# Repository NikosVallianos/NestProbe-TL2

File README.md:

# TL2 Low Cost/Power/Size High Precision Temperature Logger

This is the complete repository for the TL2 low cost/power/size temperature logger. It includes schematic and PCB layout files in EagleCAD and firmware for the ATtiny816 MCU. The Eagle files are final but the firmware is currently under prototyping-phase development and not yet published.

# List of primary components and documentation
This is a listing of the primary components used on the TL2 and links to their manufacturer's product page, where more documentation can be found.

- MCU: [Atmel/Microchip ATtiny816](https://www.microchip.com/wwwproducts/en/ATTINY816)
- Temperature sensor: [Silicon Labs Si7051](https://www.silabs.com/products/sensors/temperature/si705x/device.si7051)
- Data storage EEPROM: [Adesto AT25DN512C](https://www.adestotech.com/wp-content/uploads/DS-AT25DN512C_037.pdf) (datasheet, no product page)
- Real time clock 32.768kHz crystal: [ECS ECX-31B](https://ecsxtal.com/ecx-31b)
- Indicator amber color LED: [Kingbright APHHS1005SYCK](http://www.kingbrightusa.com/images/catalog/SPEC/APHHS1005SYCK.pdf)

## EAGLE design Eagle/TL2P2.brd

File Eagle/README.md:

Eagle cad files of the TL2 temperature logger

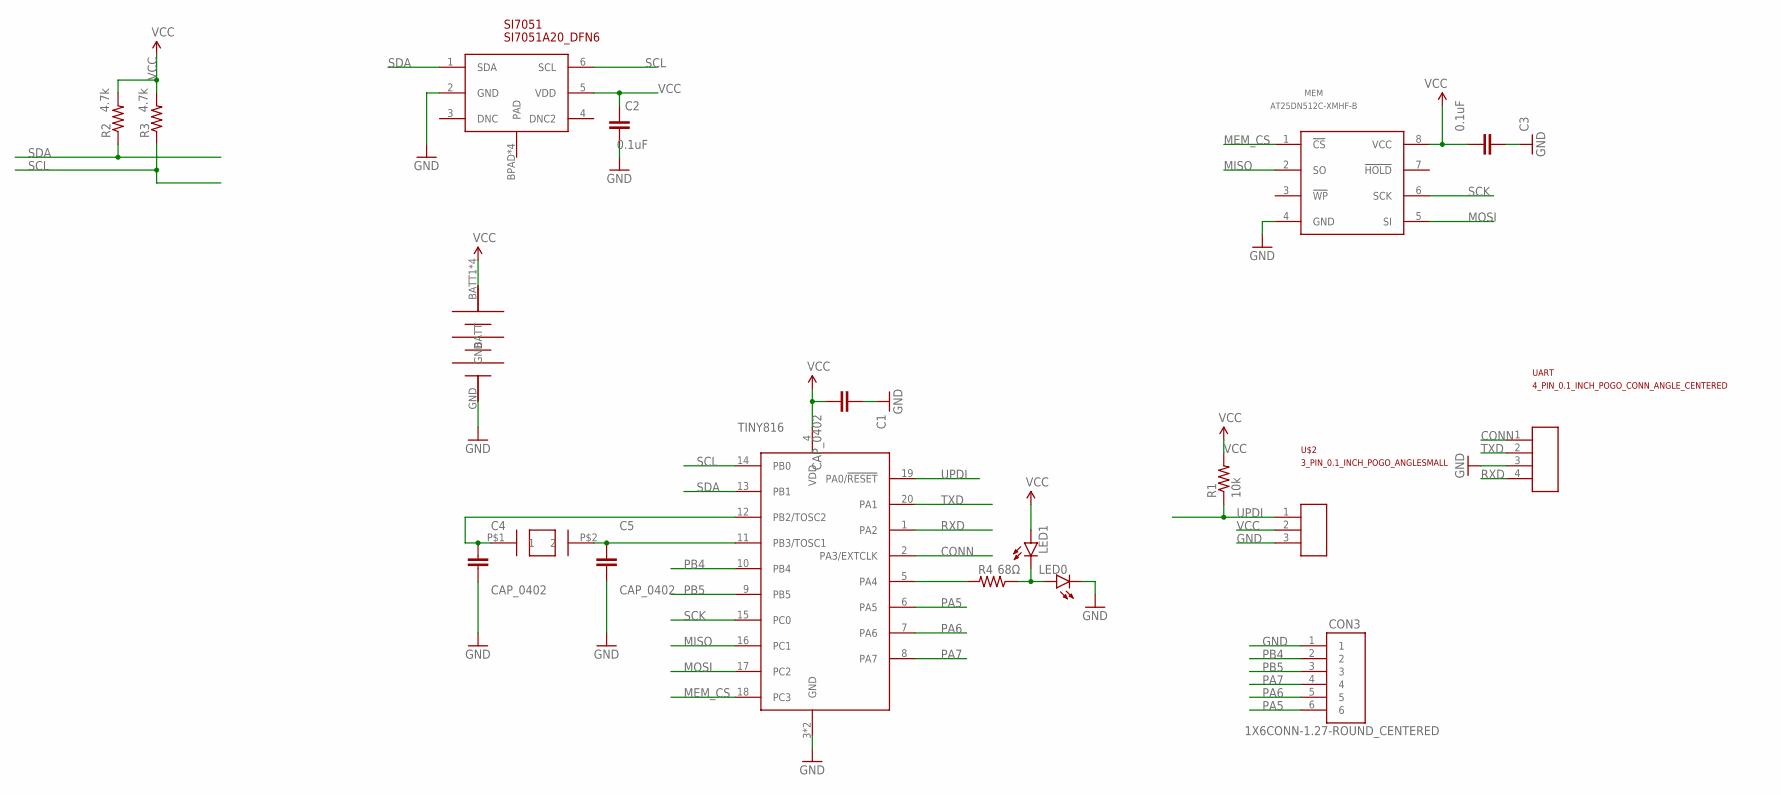
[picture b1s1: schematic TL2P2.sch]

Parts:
C1, C4, C5: CAP_0402; SMD_0402
C2, C3: 0.1uF; SMD_0402
CON3: 1X6CONN-1.27-ROUND_CENTERED; 1X6_1.27_ROUND_CENTERED
LED0, LED1: LED; SMD_0402@1
MEM: AT25DN512C-XMHF-B; TSSOP-8
R1: 10k; SMD_0402@1
R2, R3: 4.7k; SMD_0402@1
R4: 68Ω; SMD_0402@1
SI7051: SI7051A20_DFN6
T1: ABS07AIG
TINY816: ATTINY816-20; ATTINY816-VQFN20
U$1: LINX-CR2032-BAT-HLD-THM; CR2032-LINX-THM
U$2: 3_PIN_0.1_INCH_POGO_ANGLESMALL; 3_PIN_0.1INCH_POGO_ANGLE_SMALL
UART: 4_PIN_0.1_INCH_POGO_CONN_ANGLE_CENTERED; 4_PIN_0.1"_POGO_ANGLE_CENTERED

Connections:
CONN: TINY816.2 (PA3/EXTCLK), UART.1
GND: C1.1, C2.1, C3.1, C4.2, C5.2, CON3.1, LED0.2 (C), MEM.4 (GND), SI7051.2 (GND), TINY816.3 (GND), TINY816.PAD (GND), U$1.GND, U$2.3, UART.3
MEM_CS: MEM.1 (!CS!), TINY816.18 (PC3)
MISO: MEM.2 (SO), TINY816.16 (PC1)
MOSI: MEM.5 (SI), TINY816.17 (PC2)
unnamed: LED0.1 (A), LED1.2 (C), R4.2
unnamed: C5.1, T1.P$2 (2), TINY816.11 (PB3/TOSC1)
unnamed: C4.1, T1.P$1 (1), TINY816.12 (PB2/TOSC2)
PA4_LED: R4.1, TINY816.5 (PA4)
PA5: CON3.6, TINY816.6 (PA5)
PA6: CON3.5, TINY816.7 (PA6)
PA7: CON3.4, TINY816.8 (PA7)
PB4: CON3.2, TINY816.10 (PB4)
PB5: CON3.3, TINY816.9 (PB5)
RXD: TINY816.1 (PA2), UART.4
SCK: MEM.6 (SCK), TINY816.15 (PC0)
SCL: R3.2, SI7051.6 (SCL), TINY816.14 (PB0)
SDA: R2.2, SI7051.1 (SDA), TINY816.13 (PB1)
TXD: TINY816.20 (PA1), UART.2
UPDI: R1.2, TINY816.19 (PA0/!RESET!), U$2.1
VCC: C1.2, C2.2, C3.2, LED1.1 (A), MEM.8 (VCC), R1.1, R2.1, R3.1, SI7051.5 (VDD), TINY816.4 (VDD), U$1.BATT1 (BATT), U$1.BATT2 (BATT), U$1.BATT3 (BATT), U$1.BATT4 (BATT), U$2.2

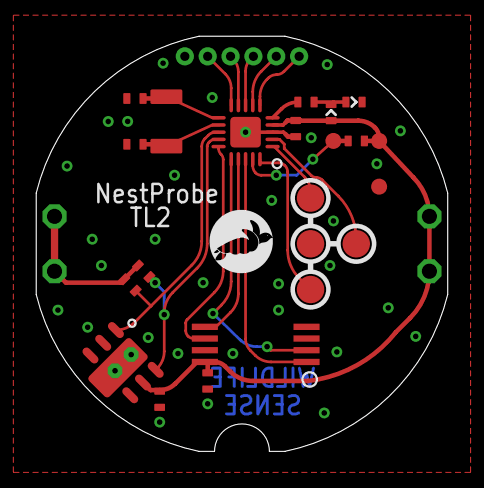
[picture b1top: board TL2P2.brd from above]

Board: 2 copper layers, 22.9 x 23.1 mm, 20 parts (1 on the bottom side), 21 nets.

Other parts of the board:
U$3: WILDLIFE-SENSE

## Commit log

2019-11-28 Added a dummy edit
2019-11-28 Cleared dummy edit

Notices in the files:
parts and their libraries:
SparkFun-Aesthetics: Licensing: Creative Commons ShareAlike 4.0 International - https://creativecommons.org/licenses/by-sa/4.0
